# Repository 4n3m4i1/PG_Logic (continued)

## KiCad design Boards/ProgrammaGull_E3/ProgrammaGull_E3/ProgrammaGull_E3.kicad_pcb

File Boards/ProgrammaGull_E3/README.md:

# ProgrammaGull E3
A flexible and light development board based on the iCE40-SG48, designed for use with project icestorm and Apio.

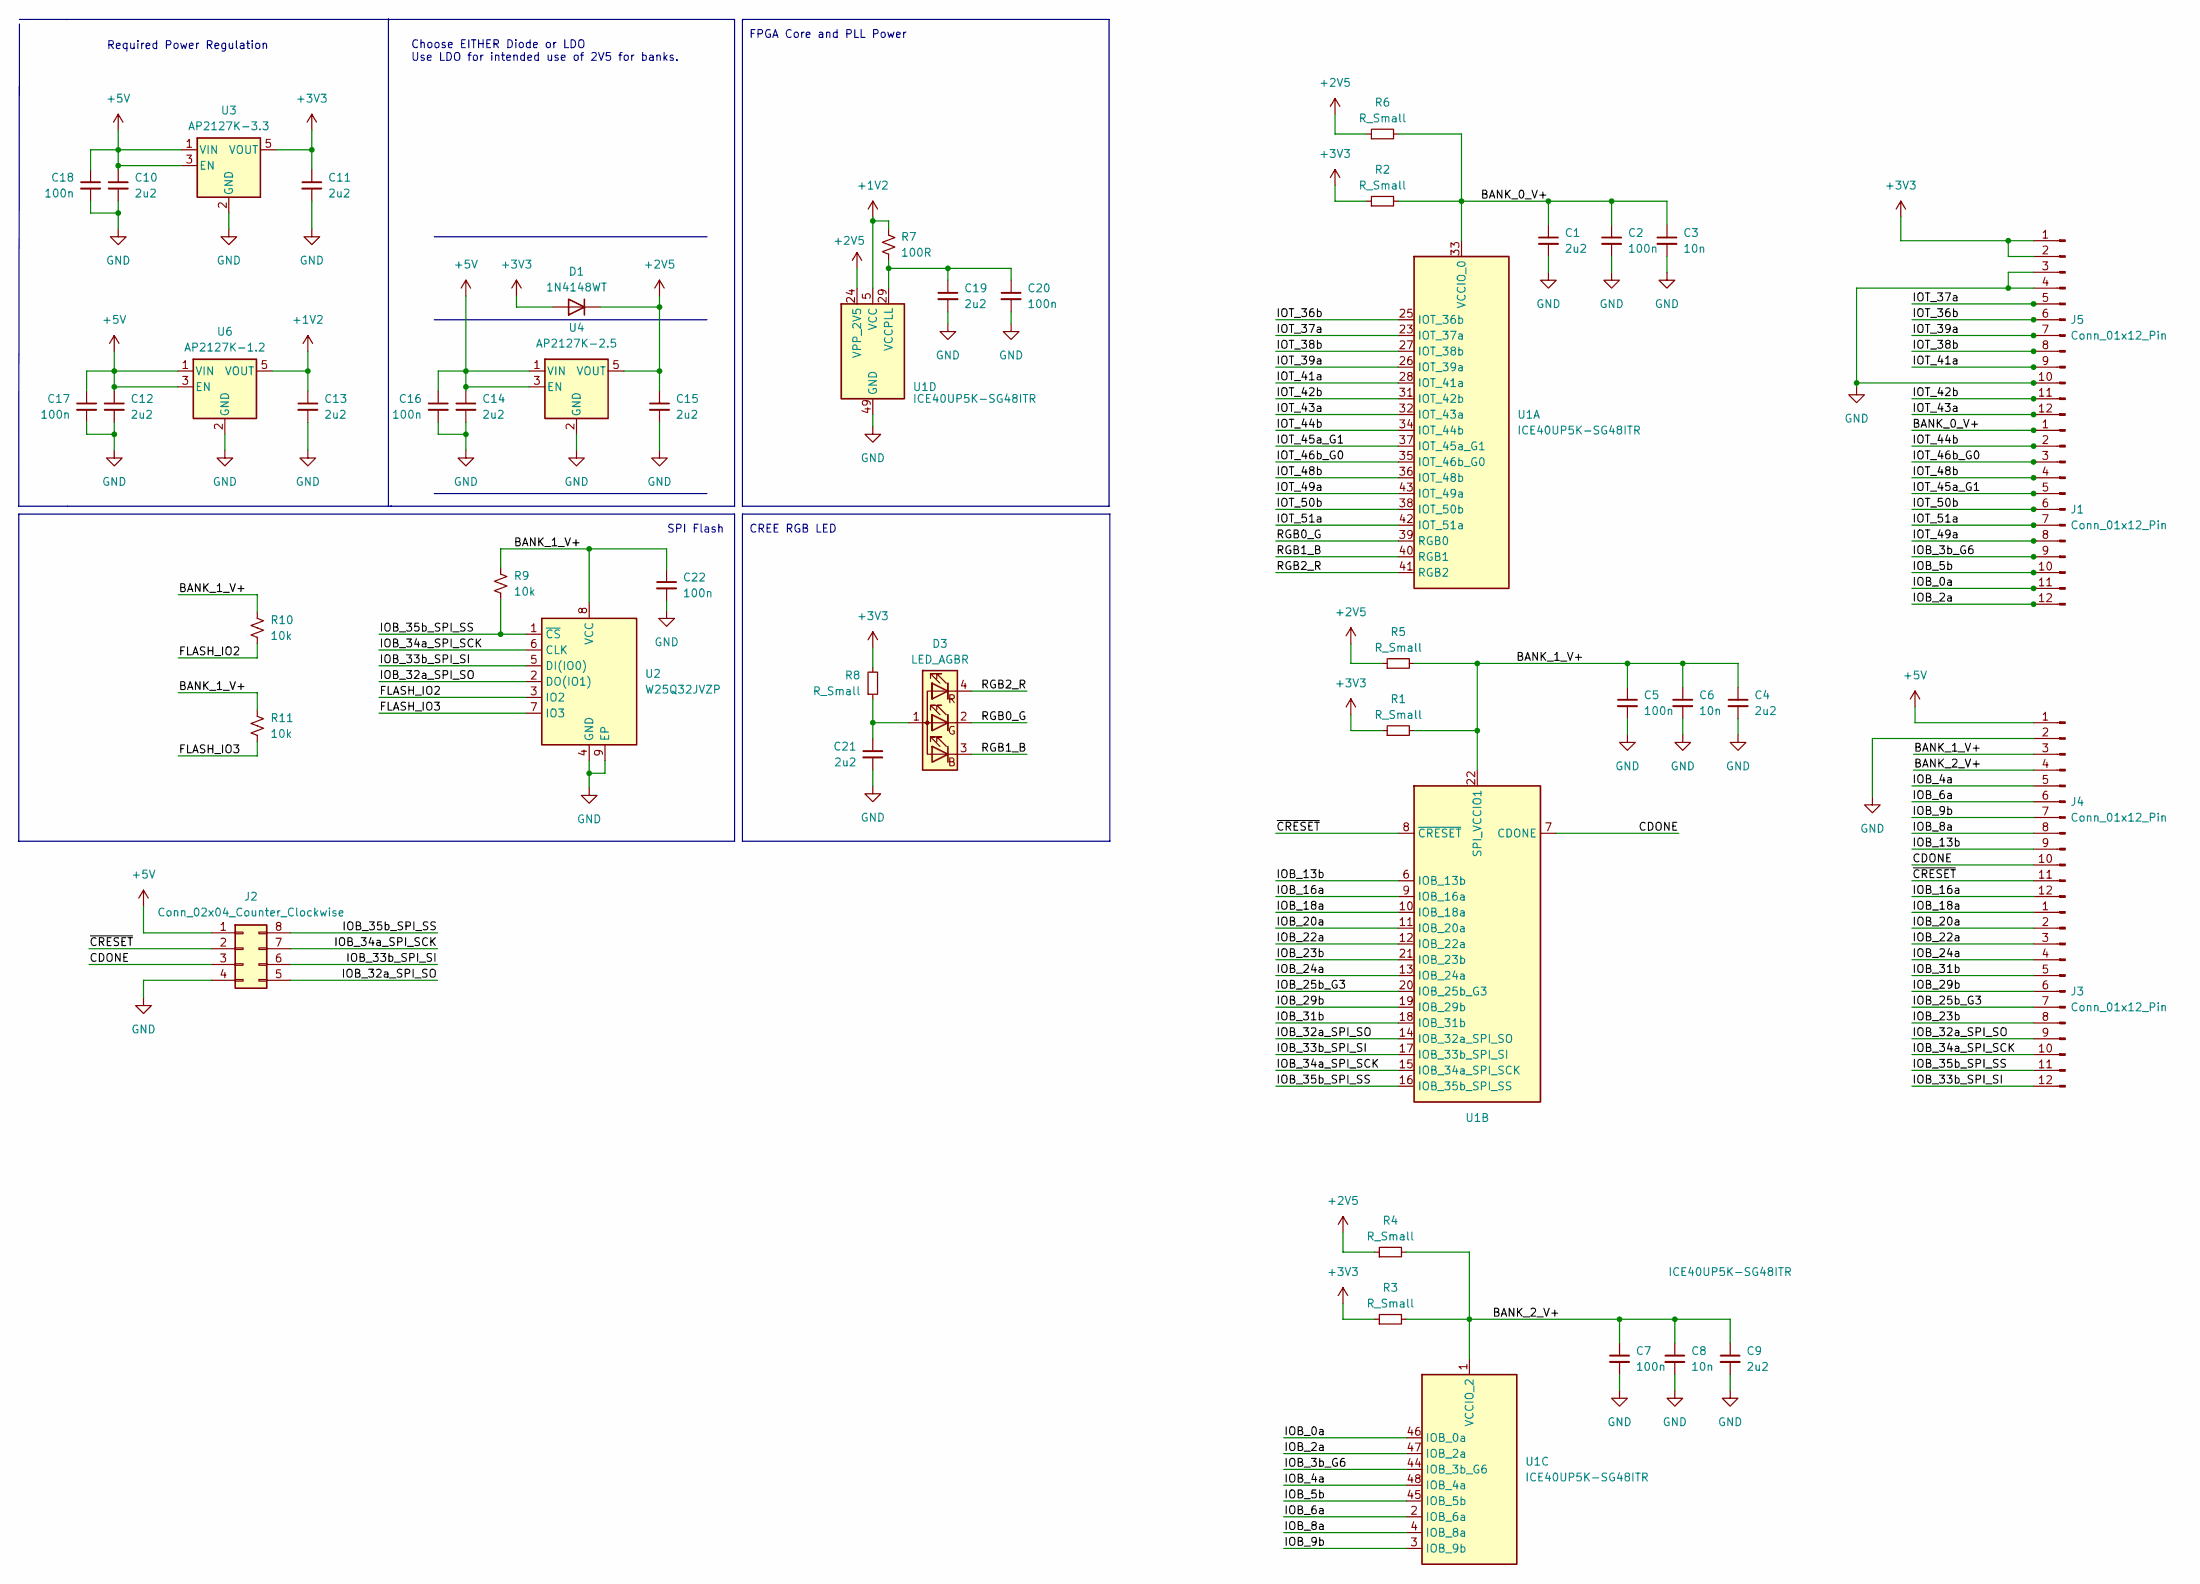
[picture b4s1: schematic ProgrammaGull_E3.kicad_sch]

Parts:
C1, C4, C9, C10, C11, C12, C13, C14, C15, C19, C21: 2u2; C_0603_1608Metric_Pad1.08x0.95mm_HandSolder
C2, C5, C7, C16, C17, C18, C20, C22: 100n; C_0603_1608Metric_Pad1.08x0.95mm_HandSolder
C3, C6, C8: 10n; C_0603_1608Metric_Pad1.08x0.95mm_HandSolder
D1: 1N4148WT; D_SOD-523
D3: LED_AGBR; LED_Cree-PLCC4_2x2mm_CW
J1, J3, J4, J5: Conn_01x12_Pin; PinSocket_1x12_P2.54mm_Vertical
J2: Conn_02x04_Counter_Clockwise; PinSocket_2x04_P2.54mm_Vertical
R1, R2, R3, R4, R5, R6, R8: R_Small; R_0603_1608Metric_Pad0.98x0.95mm_HandSolder
R7: 100R; R_0603_1608Metric_Pad0.98x0.95mm_HandSolder
R9, R10, R11: 10k; R_0603_1608Metric_Pad0.98x0.95mm_HandSolder
U1: ICE40UP5K-SG48ITR; QFN-48-1EP_7x7mm_P0.5mm_EP5.6x5.6mm
U2: W25Q32JVZP; WSON-8-1EP_6x5mm_P1.27mm_EP3.4x4.3mm
U3: AP2127K-3.3; SOT-23-5
U4: AP2127K-2.5; SOT-23-5
U6: AP2127K-1.2; SOT-23-5

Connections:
+1V2: C13.1, R7.1, U1.5 (VCC), U1.30 (VCC), U6.5 (VOUT)
+2V5: C15.1, D1.1 (K), R4.1, R5.1, R6.1, U1.24 (VPP_2V5), U4.5 (VOUT)
+3V3: C11.1, D1.2 (A), J5.1, J5.2, R1.1, R2.1, R3.1, R8.2, U3.5 (VOUT)
+5V: C10.1, C12.1, C14.1, C16.1, C17.1, C18.1, J2.1, J4.1, U3.1 (VIN), U3.3 (EN), U4.1 (VIN), U4.3 (EN), U6.1 (VIN), U6.3 (EN)
/BANK_0_V+: C1.1, C2.1, C3.1, J1.1, R2.2, R6.2, U1.33 (VCCIO_0)
/BANK_1_V+: C4.1, C5.1, C6.1, C22.1, J4.3, R1.2, R5.2, R9.1, R10.1, R11.1, U1.22 (SPI_VCCIO1), U2.8 (VCC)
/BANK_2_V+: C7.1, C8.1, C9.1, J4.4, R3.2, R4.2, U1.1 (VCCIO_2)
/CDONE: J2.3, J4.10, U1.7 (CDONE)
/FLASH_IO2: R10.2, U2.3 (IO2)
/FLASH_IO3: R11.2, U2.7 (IO3)
/IOB_0a: J1.11, U1.46 (IOB_0a)
/IOB_2a: J1.12, U1.47 (IOB_2a)
/IOB_3b_G6: J1.9, U1.44 (IOB_3b_G6)
/IOB_4a: J4.5, U1.48 (IOB_4a)
/IOB_5b: J1.10, U1.45 (IOB_5b)
/IOB_6a: J4.6, U1.2 (IOB_6a)
/IOB_8a: J4.8, U1.4 (IOB_8a)
/IOB_9b: J4.7, U1.3 (IOB_9b)
/IOB_13b: J4.9, U1.6 (IOB_13b)
/IOB_16a: J4.12, U1.9 (IOB_16a)
/IOB_18a: J3.1, U1.10 (IOB_18a)
/IOB_20a: J3.2, U1.11 (IOB_20a)
/IOB_22a: J3.3, U1.12 (IOB_22a)
/IOB_23b: J3.8, U1.21 (IOB_23b)
/IOB_24a: J3.4, U1.13 (IOB_24a)
/IOB_25b_G3: J3.7, U1.20 (IOB_25b_G3)
/IOB_29b: J3.6, U1.19 (IOB_29b)
/IOB_31b: J3.5, U1.18 (IOB_31b)
/IOB_32a_SPI_SO: J2.5, J3.9, U1.14 (IOB_32a_SPI_SO), U2.2 (DO(IO1))
/IOB_33b_SPI_SI: J2.6, J3.12, U1.17 (IOB_33b_SPI_SI), U2.5 (DI(IO0))
/IOB_34a_SPI_SCK: J2.7, J3.10, U1.15 (IOB_34a_SPI_SCK), U2.6 (CLK)
/IOB_35b_SPI_SS: J2.8, J3.11, R9.2, U1.16 (IOB_35b_SPI_SS), U2.1 (~CS)
/IOT_36b: J5.6, U1.25 (IOT_36b)
/IOT_37a: J5.5, U1.23 (IOT_37a)
/IOT_38b: J5.8, U1.27 (IOT_38b)
/IOT_39a: J5.7, U1.26 (IOT_39a)
/IOT_41a: J5.9, U1.28 (IOT_41a)
/IOT_42b: J5.11, U1.31 (IOT_42b)
/IOT_43a: J5.12, U1.32 (IOT_43a)
/IOT_44b: J1.2, U1.34 (IOT_44b)
/IOT_45a_G1: J1.5, U1.37 (IOT_45a_G1)
/IOT_46b_G0: J1.3, U1.35 (IOT_46b_G0)
/IOT_48b: J1.4, U1.36 (IOT_48b)
/IOT_49a: J1.8, U1.43 (IOT_49a)
/IOT_50b: J1.6, U1.38 (IOT_50b)
/IOT_51a: J1.7, U1.42 (IOT_51a)
/RGB0_G: D3.2 (GK), U1.39 (RGB0)
/RGB1_B: D3.3 (BK), U1.40 (RGB1)
/RGB2_R: D3.4 (RK), U1.41 (RGB2)
/~CRESET: J2.2, J4.11, U1.8 (~CRESET)
GND: C1.2, C2.2, C3.2, C4.2, C5.2, C6.2, C7.2, C8.2, C9.2, C10.2, C11.2, C12.2, C13.2, C14.2, C15.2, C16.2, C17.2, C18.2, C19.2, C20.2, C21.2, C22.2, J2.4, J4.2, J5.3, J5.4, J5.10, U1.49 (GND), U2.4 (GND), U2.9 (EP), U3.2 (GND), U4.2 (GND), U6.2 (GND)
unnamed: C21.1, D3.1 (A), R8.1
unnamed: C19.1, C20.1, R7.2, U1.29 (VCCPLL)

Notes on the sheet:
Choose EITHER Diode or LDO Use LDO for intended use of 2V5 for banks.
Required Power Regulation
CREE RGB LED
FPGA Core and PLL Power
SPI Flash

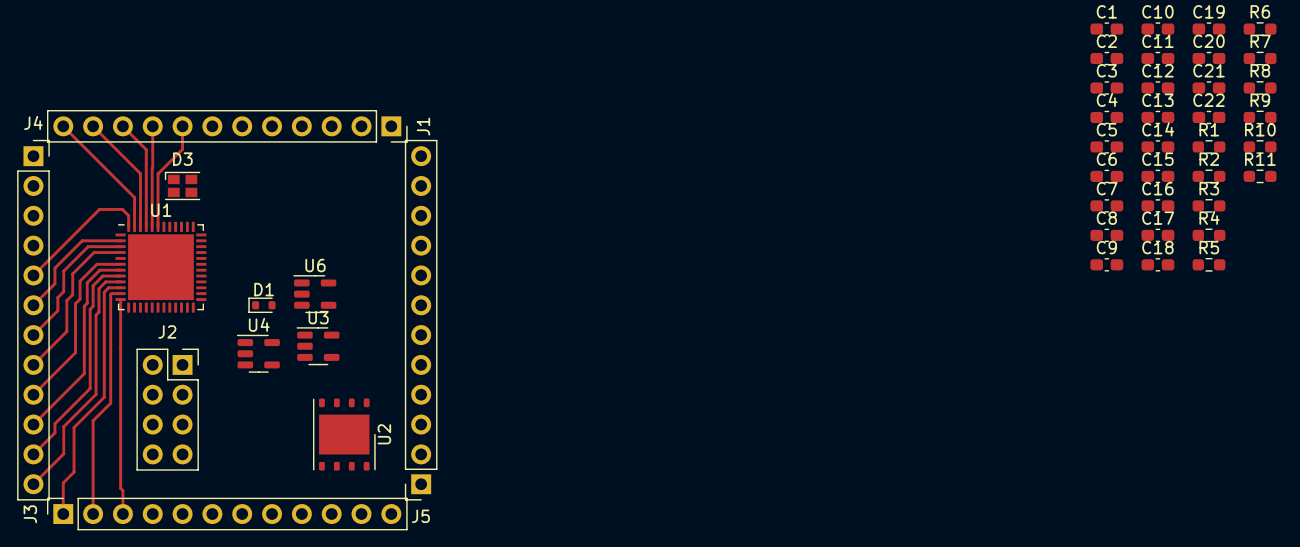
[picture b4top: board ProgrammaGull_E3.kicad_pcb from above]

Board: 2 copper layers, 45 parts (0 on the bottom side), 53 nets.

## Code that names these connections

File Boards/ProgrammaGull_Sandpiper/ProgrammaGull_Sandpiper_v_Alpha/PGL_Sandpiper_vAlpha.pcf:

#####################################
# Flash and FTDI Interface 0        #
set_io -nowarn FLASH_SCK	    15  #
set_io -nowarn FLASH_CSN	    16	# Drive high if not connected to flash.
set_io -nowarn FLASH_MISO	    17	# May need to flip MISO/MOSI perspectives
set_io -nowarn FLASH_MOSI	    14  #
                                    #
set_io -nowarn UART_RX		    19  # Data being sent FROM the FTDI to iCE40
set_io -nowarn UART_TX		    18  # Data being sent FROM the iCE40 to FTDI
#####################################

#####################################
# Bank 0: User Input, Bank 0, 3V3   #
set_io -nowarn UI_AUX_BUTTON	23  # All Button Positions:
                                    #   NO = Low, MOM = HIGH
set_io -nowarn UI_DPAD_L	    36  # 
set_io -nowarn UI_DPAD_R	    43  #
set_io -nowarn UI_DPAD_D	    42  #
set_io -nowarn UI_DPAD_U	    38  #
                                    #
set_io -nowarn UI_SW7		    25  # All Switch Positions:
set_io -nowarn UI_SW6		    26  #   UP = HIGH, DOWN = LOW
set_io -nowarn UI_SW5		    27  #
set_io -nowarn UI_SW4		    28  #
set_io -nowarn UI_SW3		    31  #
set_io -nowarn UI_SW2		    32  #
set_io -nowarn UI_SW1		    34  #
set_io -nowarn UI_SW0		    35  #
#####################################

#####################################
# External Clock, Bank 0, 3V3       #
set_io -nowarn CLK_12MHZ	    37  # Ties directly into Global Buffer 1
#####################################

#####################################
# 7 Segment Display, Common Anode   # 
set_io -nowarn UI_7SEGSR_CLK	13  #
set_io -nowarn UI_7SEGSR_RCLK	12  #
set_io -nowarn UI_7SEGSR_DIN	11  #
set_io -nowarn UI_7SEGSR_OE	    10  # LOW = Output Enabled, HIGH = Disabled
#####################################

#####################################
# 8 LED Array                       #
# Note: To fully commit a frame to  #
#       output an extra clock pulse #
#       is required due to RCLK and #
#       CLK being tied together.    #
set_io -nowarn UI_ULEDSR_CLK	21  #
set_io -nowarn UI_ULEDSR_DIN	20  #
#####################################

#####################################
# GPIO, Bank 1, 3V3                 #
set_io -nowarn UI_GPIO_0	    6   # Low Pass Alias on board for PDM
set_io -nowarn UI_GPIO_1	    9   # ^
#####################################

#####################################
# ADC SPI Interface, Bank 2, 3V3    #
set_io -nowarn UI_ADC_CSN	    44  #
set_io -nowarn UI_ADC_SCK	    45  #
set_io -nowarn UI_ADC_DI	    47  #
set_io -nowarn UI_ADC_DO	    46  #
#####################################

#####################################
# PMOD 0, Bank 2, 3V3               # 
#   1x6 pin Version                 #
set_io -nowarn UI_PMOD0_0	    48  #
set_io -nowarn UI_PMOD0_1	    2   #
set_io -nowarn UI_PMOD0_2	    3   #
set_io -nowarn UI_PMOD0_3	    4   #
#####################################

#####################################
# Common Anode RGB LED              #
# Wired to Lattice RGB LED Driver   #
set_io -nowarn UI_RGBLED_R	    41  #
set_io -nowarn UI_RGBLED_G	    39  #
set_io -nowarn UI_RGBLED_B	    40  #
#####################################

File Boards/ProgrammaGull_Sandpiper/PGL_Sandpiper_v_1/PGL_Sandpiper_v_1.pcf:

#####################################
# Flash and FTDI Interface 0        #
set_io -nowarn FLASH_SCK	    15  #
set_io -nowarn FLASH_CSN	    16	# Drive high if not connected to flash.
set_io -nowarn FLASH_MISO	    17	# May need to flip MISO/MOSI perspectives
set_io -nowarn FLASH_MOSI	    14  #
                                    #
set_io -nowarn UART_RX		    19  # Data being sent FROM the FTDI to iCE40
set_io -nowarn UART_TX		    18  # Data being sent FROM the iCE40 to FTDI
#####################################

#####################################
# Bank 0: User Input, Bank 0, 3V3   #
set_io -nowarn UI_ENC_BUTTON	27  # Encoder Button is:
set_io -nowarn UI_ENC_A	        25  #   LOW when unpressed
set_io -nowarn UI_ENC_B     	26  #   HIGH when pressed
                                    #   
set_io -nowarn UI_DPAD_L	    35  # All DPAD Button Positions:
set_io -nowarn UI_DPAD_R	    43  #   NO = Low, MOM = HIGH
set_io -nowarn UI_DPAD_D	    36  #
set_io -nowarn UI_DPAD_U	    42  #
set_io -nowarn UI_DPAD_C	    38  #
                                    #
set_io -nowarn UI_SW_D		    32  # All Switch Positions:
set_io -nowarn UI_SW_CLKEN		31  #   UP = HIGH, DOWN = LOW
set_io -nowarn UI_SW_ULED_CLK   28  #   Switches are shifted in!
set_io -nowarn UI_SW_SH_LD      34  #
#####################################

#####################################
# External Clock, Bank 0, 3V3       #
set_io -nowarn CLK_12MHZ	    37  # Ties directly into Global Buffer 1
#####################################

#####################################
# 7 Segment Display, Common Anode   # 
set_io -nowarn UI_7SEGSR_CLK	13  #
set_io -nowarn UI_7SEGSR_RCLK	12  #
set_io -nowarn UI_7SEGSR_DIN	11  #
set_io -nowarn UI_7SEGSR_OE	    10  # LOW = Output Enabled, HIGH = Disabled
#####################################

#####################################
# 8 LED Array                       #
# Note:                             #
#   Shift register clock shared     #
#   with UI_SW shift register       #
#                                   #
set_io -nowarn UI_ULEDSR_OE	    21  #
set_io -nowarn UI_ULEDSR_DIN	20  #
#####################################

#####################################
# GPIO, Bank 1, 3V3                 #
set_io -nowarn UI_GPIO_0	    6   # Low Pass Alias on board for PDM
set_io -nowarn UI_GPIO_1	    9   # ^
#####################################

#####################################
# ADC SPI Interface, Bank 2, 3V3    #
set_io -nowarn UI_ADC_CSN	    44  #
set_io -nowarn UI_ADC_SCK	    45  #
set_io -nowarn UI_ADC_DI	    47  #
set_io -nowarn UI_ADC_DO	    46  #
#####################################

#####################################
# PMOD 0, Bank 2, 3V3               # 
#   1x6 pin Version                 #
set_io -nowarn UI_PMOD0_0	    4   #
set_io -nowarn UI_PMOD0_1	    3   #
set_io -nowarn UI_PMOD0_2	    2   #
set_io -nowarn UI_PMOD0_3	    48  #
#####################################

#####################################
# Common Anode RGB LED              #
# Wired to Lattice RGB LED Driver   #
set_io -nowarn UI_RGBLED_R	    41  #
set_io -nowarn UI_RGBLED_G	    39  #
set_io -nowarn UI_RGBLED_B	    40  #
#####################################

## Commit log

2023-09-16 Initial E3 commit
2023-10-30 Initial Sandpiper Commit
2023-11-01 Big Sandpiper updates :)
2023-11-01 Sandpiper Progress!
2023-11-06 Alpha Sandpiper Board Completegit status
2023-11-07 Fixed 7 segment drive circuitry to work properly, swap to 74 596 + segment brightness limiting resistors
2023-11-08 Adjustments made to better fit JLC/LCSC Parts Library
2023-11-09 Final Alpha Version
2023-11-09 Added Sandpiper README
2023-11-10 Final Sandpiper Alpha Changes, just cleanup.
2023-11-10 Update PGL Sandpiper README
2023-11-15 Updated gitignore
2023-11-15 Added PGL E6 project files, Sandpiper Alpha Schematic
2023-11-15 Addedd PCF for Sandpiper Alpha
2023-11-18 eeprom configuration for Sandpiper Alpha
2023-11-18 Errata: Fixed reversed LEDs on FTDI.... oops :)
2023-11-18 same
2023-11-18 Updated board revision for Alpha
2023-11-25 Minor Adds, small fixes on Sandpiper PCB
2023-11-26 Hardware issue found with Sandpiper 7 Seg PNP array, looking into it
2023-11-26 Updated Sandpiper v.Alpha Errata :(
2023-11-26 Segments -> Digits
2023-11-27 In progress conversion to maintaining 5V on seven segment
2023-11-27 Converted to 3v3 7 segment drive voltage
2023-11-27 Sandpiper Alpha Schematic updated for new 7 segment drive strategy
2023-11-27 Small fixes in example
2024-01-07 Sandpiper first release almost done :)
2024-01-22 Final revision Sandpiper V1, sent for fab
2024-02-06 Updated Sandpiper V1 PCF to match schematic
2024-02-09 Added PGL FT2232HQ generic programmer :)
2024-02-12 PGL Programmer Test Run Finished
2024-02-13 Skimmer init
2024-02-14 Mostly working example for Sandpiper v.1
2024-02-15 Expanding device drivers for Sandpiper V1
2024-02-20 Added Sandpiper V1 DDS Example, currently only variable frequency sine
2024-07-30 Sync
2024-07-31 PGL E3 Start
2024-08-06 E6 layout redo
